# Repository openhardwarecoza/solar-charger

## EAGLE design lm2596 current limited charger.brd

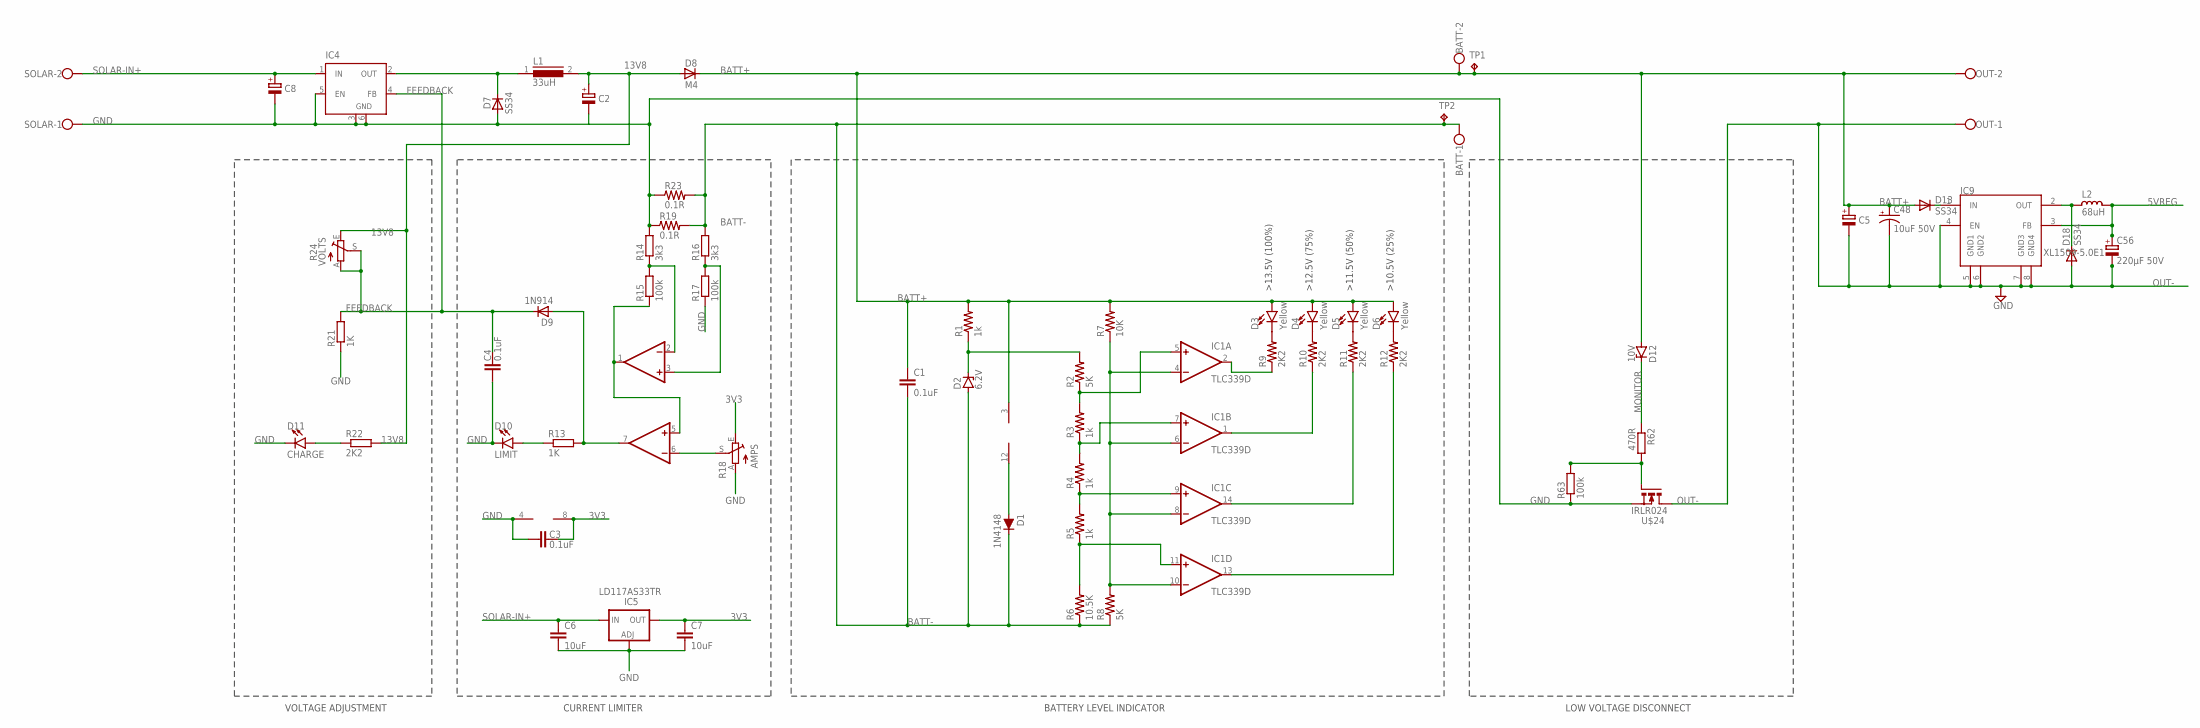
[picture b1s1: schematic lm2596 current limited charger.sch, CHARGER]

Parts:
BATT: W237-102
C1, C3, C4: 0.1uF; C1206K
C2, C5, C8: CPOL-EUE3.5-8; E3,5-8
C6, C7: 10uF; C1206K
C48: 10uF 50V; EIA3216
C56: 220µF 50V; E3,5-10
D1: 1N4148; SOD-323
D2: 6.2V; SMB
D3, D4, D5, D6: Yellow; LED-1206
D7: SS34; SOD87
D8: M4; SOD87
D9: 1N914; SOD87
D10: LIMIT; LED-1206
D11: CHARGE; LED-1206
D12: 10V; SMB
D13, D18: SS34; DO-214AC
IC1: TLC339D; SO14
IC2: MCP602SN; SO08
IC4: LM2596S; TO263-5
IC5: LD117AS33TR; SOT223
IC9: XL1509-5.0E1; SO08
L1: 33uH; DR127
L2: 68uH; CD75
OUT: W237-102
R1, R3, R4, R5: 1k; R1206
R2, R8: 5K; R1206
R6: 10.5K; R1206
R7: 10K; R1206
R9, R10, R11, R12, R22: 2K2; R1206
R13, R21: 1K; R1206
R14, R16: 3k3; R1206
R15, R17: 100k; R1206
R18: AMPS; B64Y
R19, R23: 0.1R; R2512
R24: VOLTS; B64Y
R62: 470R; R0603
R63: 100k; R0603
SOLAR: W237-102
TP1, TP2: TPPAD1-20Y; P1-20Y
U$24: IRLR024; D-PAK_TO252AA

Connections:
3V3: C3.2, C7.1, IC2.8 (V+), IC5.4 (OUT), R18.E
5VREG: C56.+, IC9.3 (FB), L2.1
13V8: C2.+, D8.2 (A), L1.2, R22.2, R24.E
BATT+: BATT.2, C1.1, C5.+, C48.A (+), D3.A, D4.A, D5.A, D6.A, D8.1 (C), D12.A, D13.2 (A), IC1.3 (V+), OUT.2, R1.2, R7.2, TP1.TP
BATT-: BATT.1, C1.2, D1.C, D2.A, R6.1, R8.1, R16.2, R19.2, R23.2, TP2.TP
FEEDBACK: C4.2, D9.1 (C), IC4.4 (FB), R21.2, R24.A, R24.S
GND: C2.-, C3.1, C4.1, C6.2, C7.2, C8.-, D7.2 (A), D10.C, D11.C, IC2.4 (V-), IC4.3 (GND), IC4.5 (EN), IC4.6 (GND), IC5.1 (ADJ), R14.2, R17.1, R18.A, R19.1, R21.1, R23.1, R63.1, SOLAR.1, U$24.3 (S)
MONITOR: D12.C, R62.1
unnamed: D7.1 (C), IC4.2 (OUT), L1.1
unnamed: D2.C, R1.1, R2.2
unnamed: IC1.5 (+IN), R2.1, R3.2
unnamed: IC1.7 (+IN), R3.1, R4.2
unnamed: IC1.9 (+IN), R4.1, R5.2
unnamed: IC1.11 (+IN), R5.1, R6.2
unnamed: IC1.4 (-IN), IC1.6 (-IN), IC1.8 (-IN), IC1.10 (-IN), R7.1, R8.2
unnamed: D3.C, R9.2
unnamed: D4.C, R10.2
unnamed: D5.C, R11.2
unnamed: D6.C, R12.2
unnamed: R62.2, R63.2, U$24.1 (G)
unnamed: IC1.2 (OUT), R9.1
unnamed: IC1.1 (OUT), R10.1
unnamed: IC1.14 (OUT), R11.1
unnamed: IC1.13 (OUT), R12.1
unnamed: D1.A, IC1.12 (V-)
unnamed: D9.2 (A), IC2.7 (OUT), R13.2
unnamed: IC2.6 (-IN), R18.S
unnamed: D10.A, R13.1
unnamed: IC2.1 (OUT), IC2.5 (+IN), R15.1
unnamed: D11.A, R22.1
unnamed: IC2.3 (+IN), R16.1, R17.2
unnamed: IC2.2 (-IN), R14.1, R15.2
unnamed: D18.1 (C), IC9.2 (OUT), L2.2
unnamed: D13.1 (C), IC9.1 (IN)
OUT-: C5.-, C48.C (-), C56.-, D18.2 (A), IC9.4 (EN), IC9.5 (GND1), IC9.6 (GND2), IC9.7 (GND3), IC9.8 (GND4), OUT.1, U$24.4 (D)
SOLAR-IN+: C6.1, C8.+, IC4.1 (IN), IC5.3 (IN), SOLAR.2

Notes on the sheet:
CURRENT LIMITER
VOLTAGE ADJUSTMENT
LOW VOLTAGE DISCONNECT
BATTERY LEVEL INDICATOR

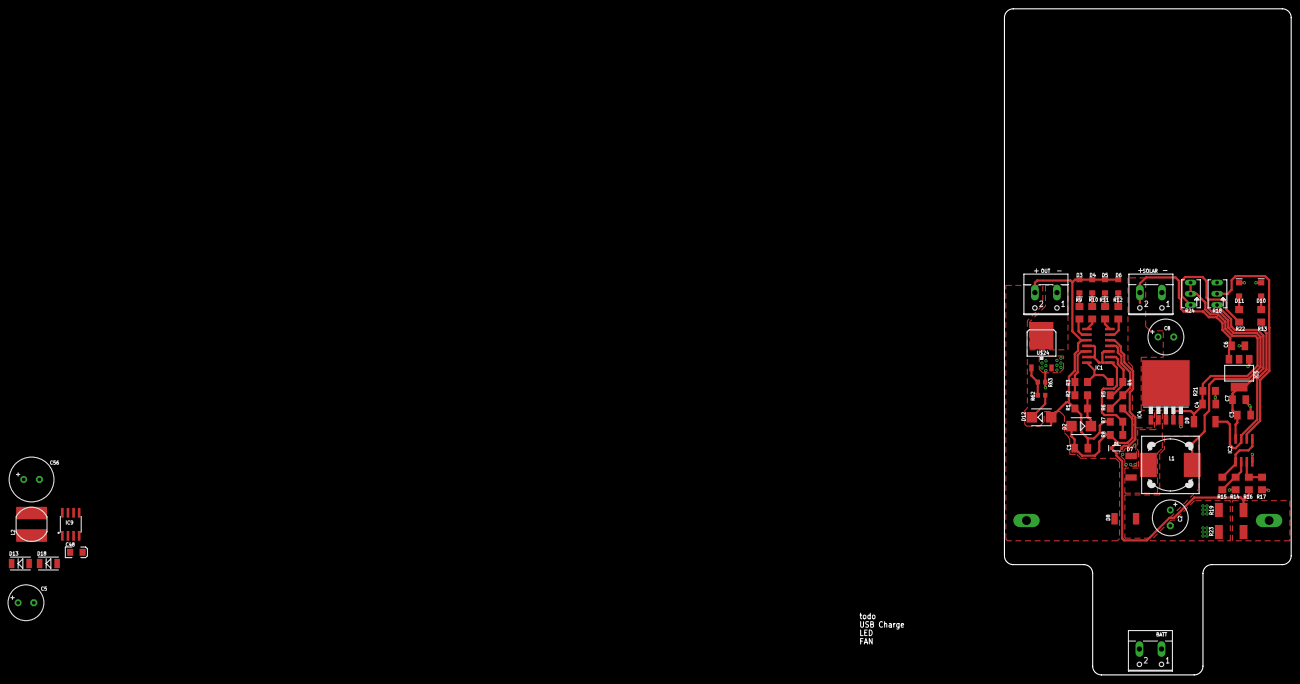
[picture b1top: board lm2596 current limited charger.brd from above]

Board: 2 copper layers, 65.0 x 151.0 mm, 62 parts (0 on the bottom side), 36 nets.

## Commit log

2019-12-13 schematic
2019-12-16 as ordered

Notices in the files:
parts and their libraries:
SparkFun-DiscreteSemi: Licensing: Creative Commons ShareAlike 4.0 International - https://creativecommons.org/licenses/by-sa/4.0
rc-master-smd: Copyright (C) 2007, Bob Starr
